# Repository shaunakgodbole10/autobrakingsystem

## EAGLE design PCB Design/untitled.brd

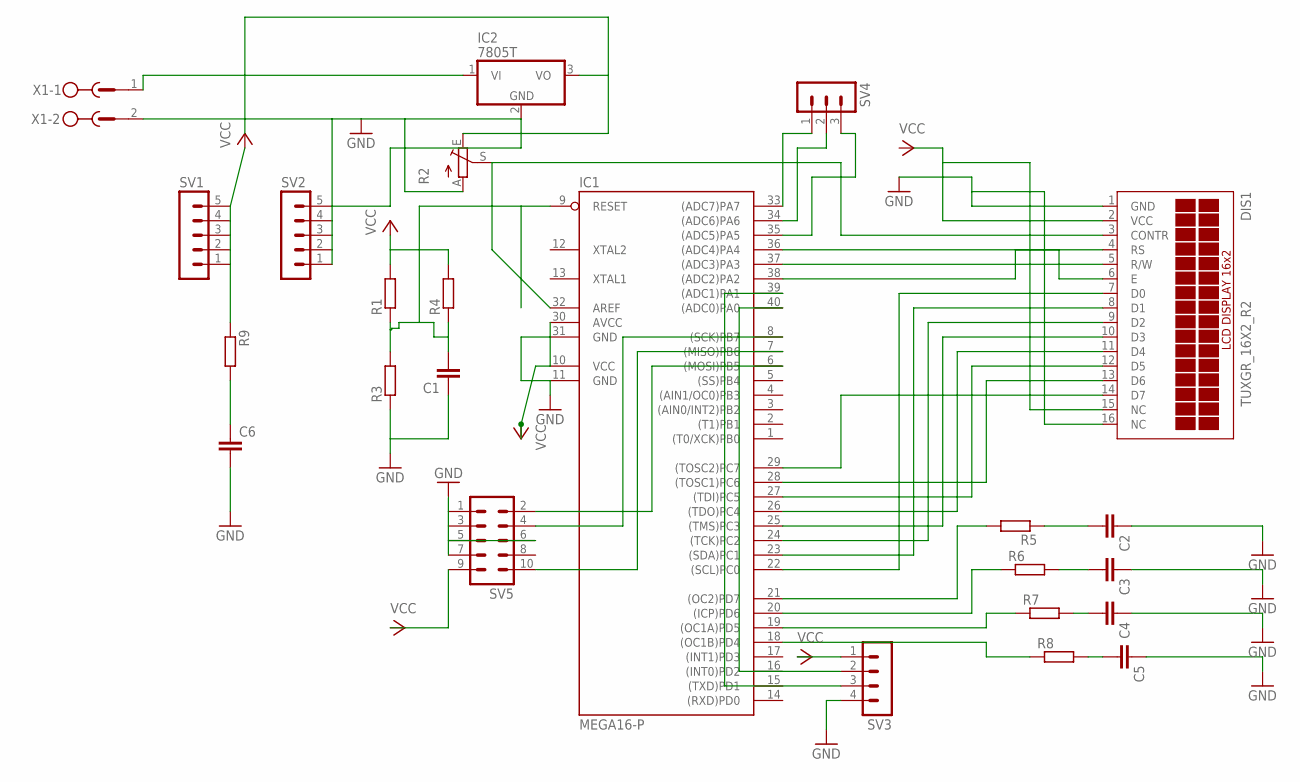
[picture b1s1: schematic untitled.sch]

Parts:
C1, C2, C3, C4, C5, C6: C-EU025-025X050; C025-025X050
DIS1: TUXGR_16X2_R2
IC1: MEGA16-P; DIL40
IC2: 7805T; TO220H
R1, R4, R5, R6, R7, R8, R9: R-EU_0207/7; 0207/7
R2: TRIM_EU-B25X; B25X
R3: R-EU_0207/5V; 0207/5V
SV1, SV2: MA05-1
SV3: MA04-1
SV4: MA03-1
SV5: MA05-2
X1: MSTBV2

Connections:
GND: C1.1, C2.1, C3.1, C4.1, C5.1, C6.2, DIS1.1 (GND), DIS1.16 (NC), IC1.11 (GND), IC1.31 (GND), IC2.2 (GND), R2.A, R3.1, SV2.1, SV2.2, SV2.3, SV2.4, SV2.5, SV3.4, SV5.1, SV5.3, SV5.5, SV5.6, SV5.7, X1.2
unnamed: IC1.10 (VCC), IC1.30 (AVCC)
unnamed: DIS1.2 (VCC), DIS1.15 (NC)
unnamed: IC2.3 (VO), R2.E
unnamed: C1.2, IC1.9 (RESET), R1.1, R3.2, R4.1
unnamed: DIS1.4 (RS), IC1.38 ((ADC2)PA2)
unnamed: DIS1.5 (R/W), IC1.37 ((ADC3)PA3)
unnamed: DIS1.6 (E), IC1.36 ((ADC4)PA4)
unnamed: DIS1.7 (D0), IC1.22 ((SCL)PC0)
unnamed: DIS1.8 (D1), IC1.23 ((SDA)PC1)
unnamed: DIS1.9 (D2), IC1.24 ((TCK)PC2)
unnamed: DIS1.10 (D3), IC1.25 ((TMS)PC3)
unnamed: DIS1.11 (D4), IC1.26 ((TDO)PC4)
unnamed: DIS1.12 (D5), IC1.27 ((TDI)PC5)
unnamed: DIS1.13 (D6), IC1.28 ((TOSC1)PC6)
unnamed: DIS1.14 (D7), IC1.29 ((TOSC2)PC7)
unnamed: IC1.40 ((ADC0)PA0), SV3.2
unnamed: IC1.39 ((ADC1)PA1), SV3.3
unnamed: IC1.7 ((MISO)PB6), SV5.10
unnamed: IC1.6 ((MOSI)PB5), SV5.2
unnamed: IC1.8 ((SCK)PB7), SV5.4
unnamed: IC1.33 ((ADC7)PA7), SV4.1
unnamed: IC1.34 ((ADC6)PA6), SV4.2
unnamed: IC1.35 ((ADC5)PA5), SV4.3
unnamed: IC1.21 ((OC2)PD7), R5.2
unnamed: C2.2, R5.1
unnamed: IC1.20 ((ICP)PD6), R6.1
unnamed: C3.2, R6.2
unnamed: IC1.19 ((OC1A)PD5), R7.1
unnamed: C4.2, R7.2
unnamed: IC1.18 ((OC1B)PD4), R8.1
unnamed: C5.2, R8.2
unnamed: C6.1, R9.2
unnamed: IC2.1 (VI), X1.1
unnamed: DIS1.3 (CONTR), IC1.32 (AREF), R2.S
VCC: R1.2, R4.2, R9.1, SV1.1, SV1.2, SV1.3, SV1.4, SV1.5, SV3.1, SV5.9

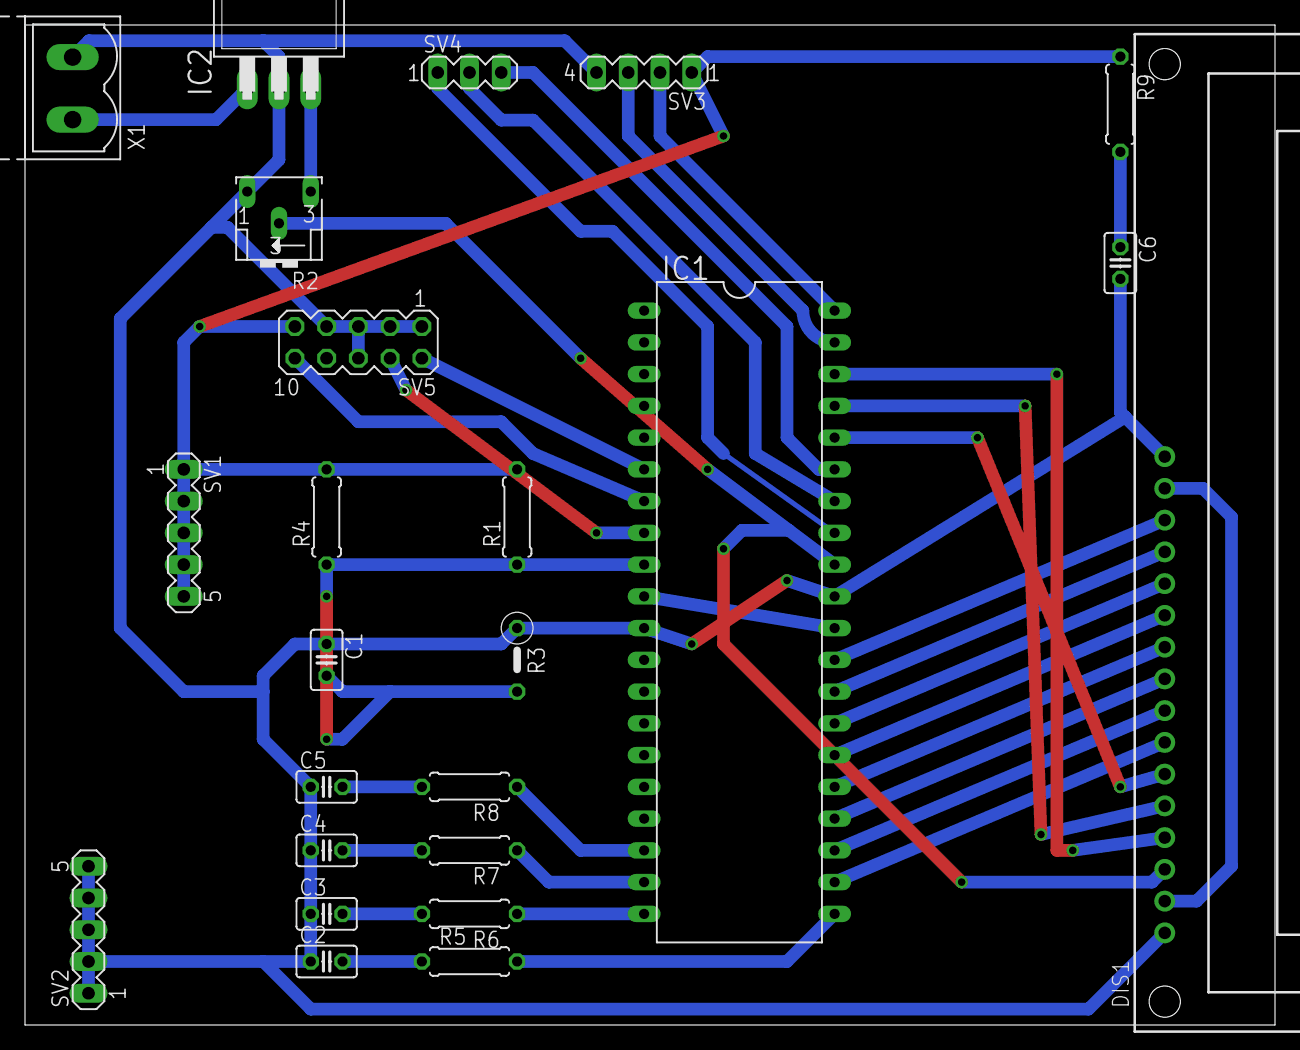
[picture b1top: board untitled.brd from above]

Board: 2 copper layers, 100.0 x 80.0 mm, 24 parts (0 on the bottom side), 36 nets.

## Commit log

2018-11-14 second commit
